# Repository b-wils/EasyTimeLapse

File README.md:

# Easy Time Lapse

Easy Time Lapse (ETL) is device that allows enables you DSLR camera to capture timelapses. 

You can read on overview of the project here-
https://web.archive.org/web/20150224155257/http://nerdtribe.blog.com:80/easy-time-lapse
https://web.archive.org/web/20130428181341/http://scramblor.posterous.com

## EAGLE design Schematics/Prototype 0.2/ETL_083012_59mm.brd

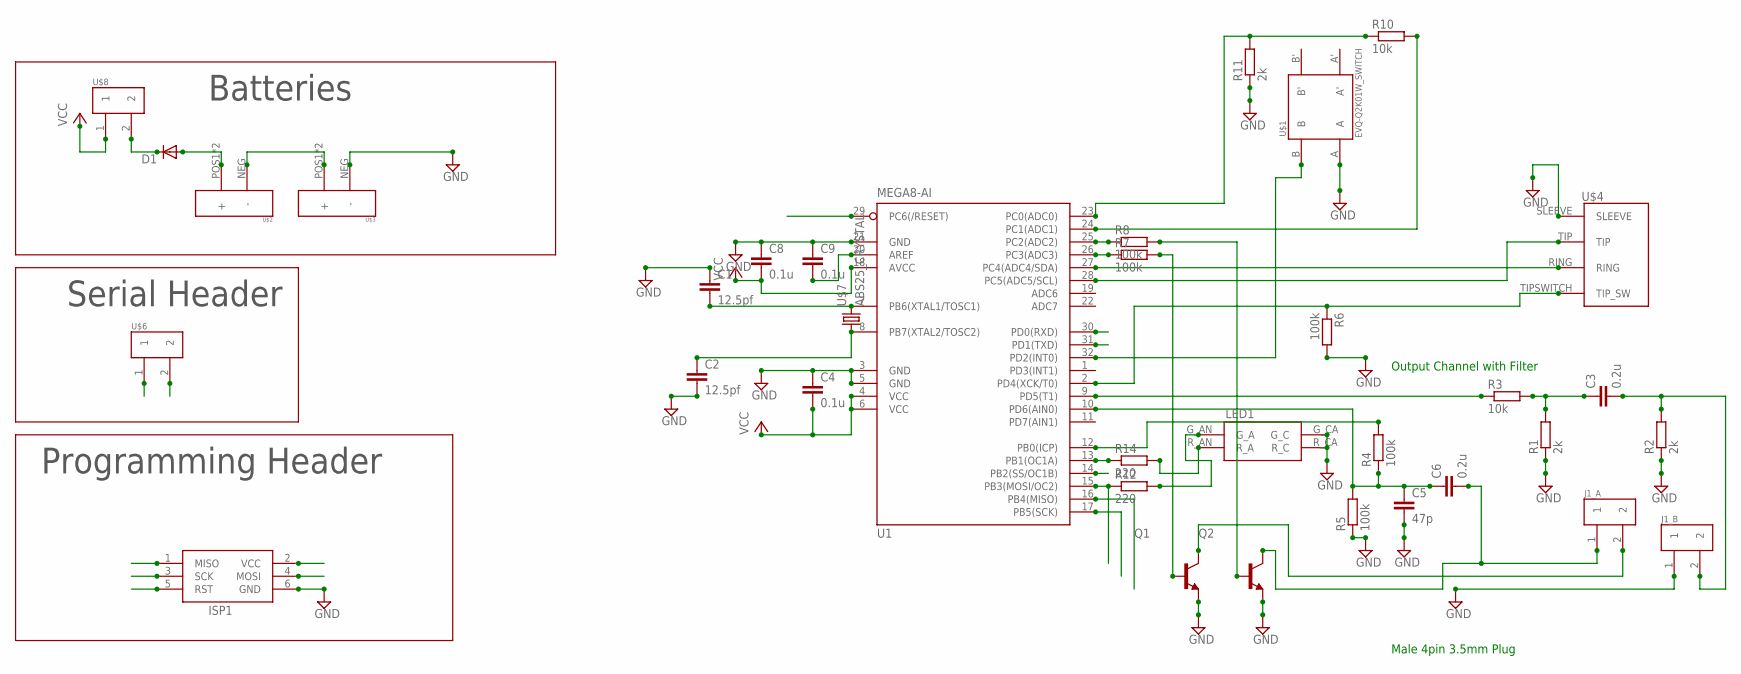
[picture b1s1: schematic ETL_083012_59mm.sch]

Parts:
C1, C2: 12.5pf; C0402
C3, C6: 0.2u; C0402
C4, C8, C9: 0.1u; C0402
C5: 47p; C0402
D1: DIODE-SOD323-R; SOD323-R
ISP1: AVRISP-6; AVRISP
J1_A, J1_B: SERIAL_2_VERT
LED1: LED_BI_RG; LED_BI_1210
Q1, Q2: BC847-NPN-SOT23-BEC; SOT23-BEC
R1, R2, R11: 2k; R0402
R3, R10: 10k; R0402
R4, R5, R6, R7, R8: 100k; R0402
R12, R14: 220; R0402
U1: MEGA8-AI; TQFP32-08
U$1: EVQ-Q2K01W_SWITCH
U$2, U$3: 22M2620_BATTHOLDER
U$4: SJ-3524-SMT_AUDIOJACK
U$6, U$8: SERIAL_2_VERT
U$7: ABS25_CRYSTAL

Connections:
GND: C1.1, C2.2, C4.1, C5.2, C8.1, C9.1, ISP1.6 (GND), J1_B.1, LED1.G_CA (G_C), LED1.R_CA (R_C), Q1.E, Q2.E, R1.1, R2.1, R5.1, R6.2, R11.1, U1.3 (GND), U1.5 (GND), U1.21 (GND), U$1.A, U$3.NEG (-), U$4.SLEEVE
MISO: ISP1.1 (MISO), U1.16 (PB4(MISO))
MOSI: ISP1.4 (MOSI), R12.1, U1.15 (PB3(MOSI/OC2))
unnamed: C1.2, U1.7 (PB6(XTAL1/TOSC1)), U$7.4 (2)
unnamed: C2.1, U1.8 (PB7(XTAL2/TOSC2)), U$7.1
unnamed: R14.1, U1.13 (PB1(OC1A))
unnamed: LED1.G_AN (G_A), R12.2
unnamed: D1.C, U$8.2
unnamed: LED1.R_AN (R_A), R14.2
unnamed: R3.1, U1.9 (PD5(T1))
unnamed: C5.1, C6.1, R4.1, R5.2, U1.10 (PD6(AIN0))
unnamed: C3.1, R1.2, R3.2
unnamed: C3.2, J1_B.2, R2.2
unnamed: R8.1, U1.25 (PC2(ADC2))
unnamed: R10.2, U1.24 (PC1(ADC1))
unnamed: R7.1, U1.26 (PC3(ADC3))
unnamed: U$2.NEG (-), U$3.POS1 (+), U$3.POS2 (+)
unnamed: C9.2, U1.20 (AREF)
unnamed: R10.1, R11.2, U1.23 (PC0(ADC0))
unnamed: Q1.B, R7.2
unnamed: Q2.B, R8.2
unnamed: U1.32 (PD2(INT0)), U$1.B
unnamed: D1.A, U$2.POS1 (+), U$2.POS2 (+)
unnamed: J1_A.2, Q1.C
unnamed: C6.2, J1_A.1, Q2.C
unnamed: R4.2, U1.12 (PB0(ICP))
PC4: U1.27 (PC4(ADC4/SDA)), U$4.RING
PC5: U1.28 (PC5(ADC5/SCL)), U$4.TIP
PD0: U1.30 (PD0(RXD)), U$6.1
PD1: U1.31 (PD1(TXD)), U$6.2
PD4: R6.1, U1.2 (PD4(XCK/T0)), U$4.TIPSWITCH (TIP_SW)
RESET: ISP1.5 (RST), U1.29 (PC6(/RESET))
SCK: ISP1.3 (SCK), U1.17 (PB5(SCK))
VCC: C4.2, C8.2, ISP1.2 (VCC), U1.4 (VCC), U1.6 (VCC), U1.18 (AVCC), U$8.1

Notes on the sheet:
Output Channel with Filter
Male 4pin 3.5mm Plug
Batteries
Serial Header
Programming Header

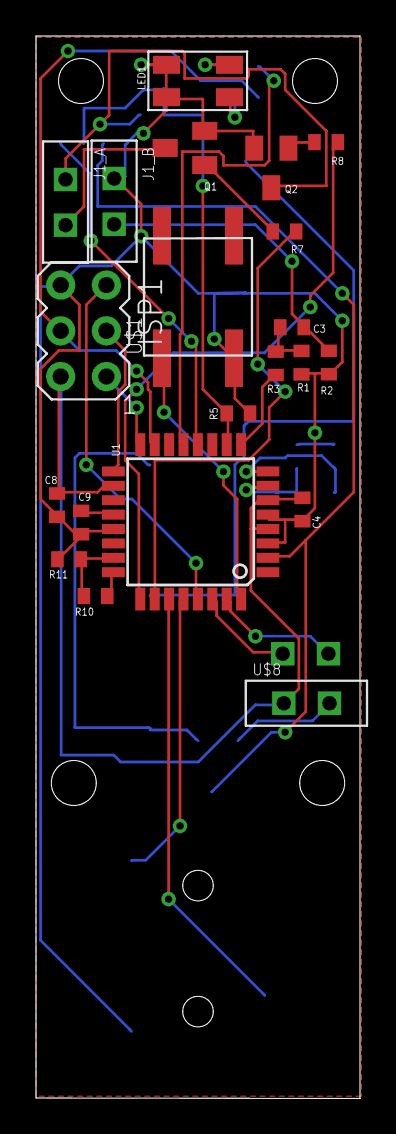
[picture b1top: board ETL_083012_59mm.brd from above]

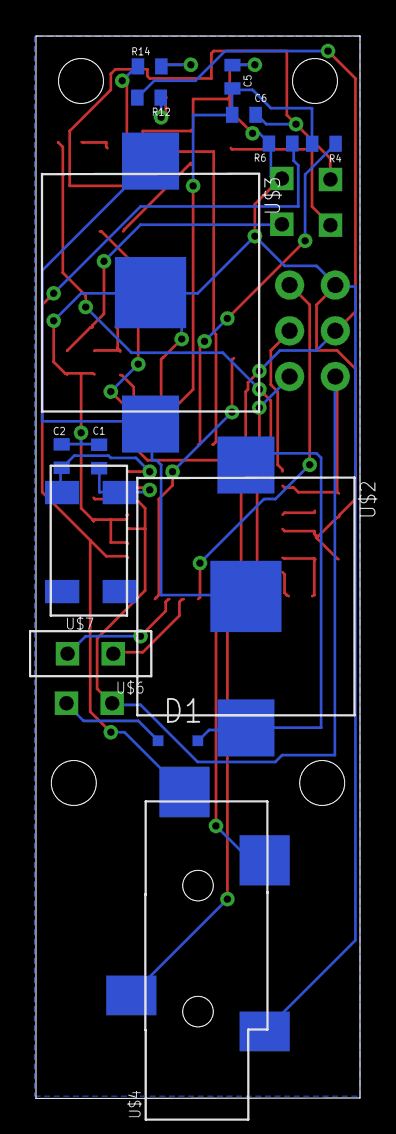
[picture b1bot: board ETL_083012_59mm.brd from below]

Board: 2 copper layers, 18.0 x 59.0 mm, 35 parts (14 on the bottom side), 34 nets.

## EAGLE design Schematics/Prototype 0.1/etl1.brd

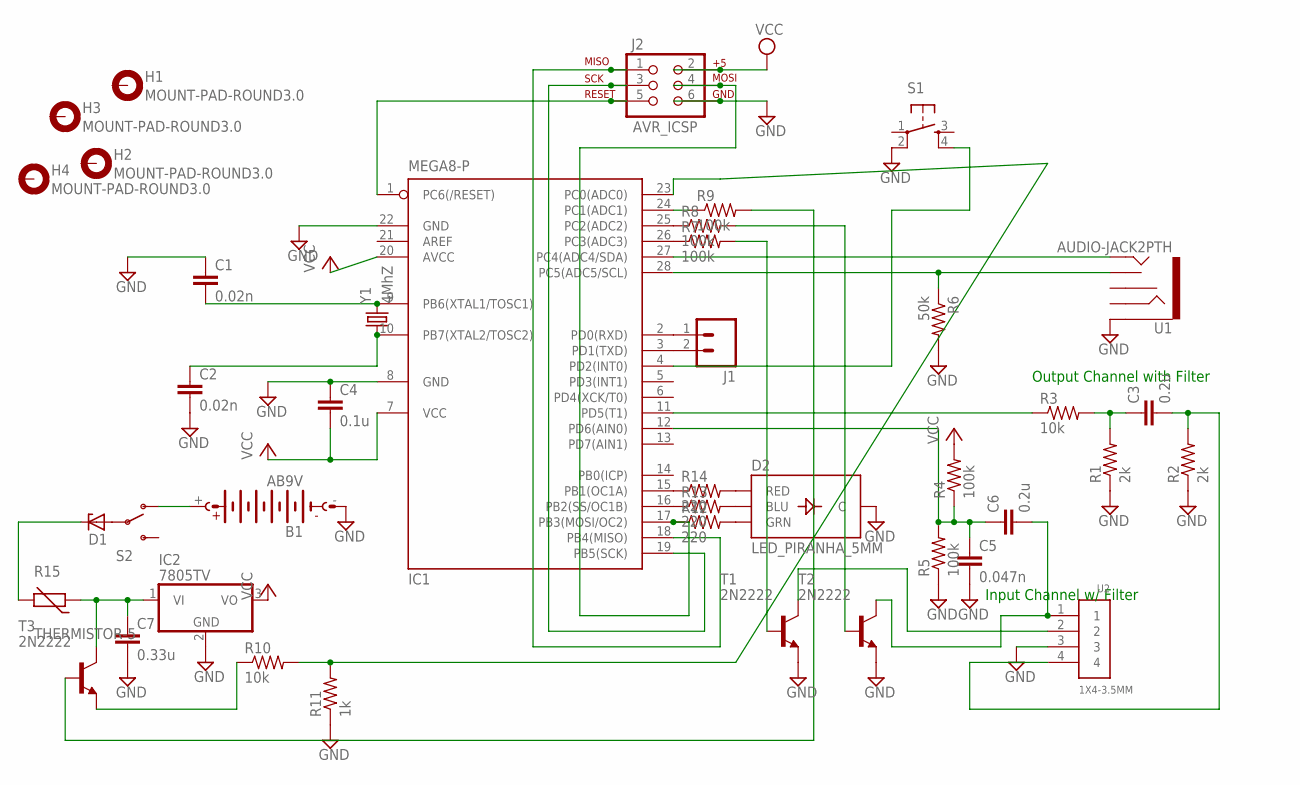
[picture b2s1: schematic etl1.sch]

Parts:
B1: AB9V
C1, C2: 0.02n; C5B3
C3, C6: 0.2u; C5B3
C4: 0.1u; C5B3
C5: 0.047n; C5B3
C7: 0.33u; C5B3
D1: ZENER-DIODEZD-10; ZDIO-10
D2: LED_PIRANHA_5MM
H1, H2, H3, H4: MOUNT-PAD-ROUND3.0; 3,0-PAD
IC1: MEGA8-P; DIL28-3
IC2: 7805TV; TO220V
J1: M02LOCK; 1X02_LOCK
J2: AVR_ICSP; 2X3-NS
R1, R2: 2k; 0207/10
R3, R10: 10k; 0207/10
R4, R5, R7, R8, R9: 100k; 0207/10
R6: 50k; 0207/10
R11: 1k; 0207/10
R12, R13, R14: 220; 0207/10
R15: THERMISTOR-5; R-5
S1: TAC_SWITCHPTH; TACTILE-PTH
S2: SWITCH-SPDTPTH; SWITCH-SPDT
T1, T2, T3: 2N2222; TO92-EBC-OVAL
U1: AUDIO-JACK2PTH; AUDIO-JACK
U2: 1X4-3.5MM; 1X04-3.5MM
Y1: 4MhZ; HC49US

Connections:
GND: B1.-, C1.1, C2.2, C4.1, C5.2, C7.2, D2.- (C), IC1.8 (GND), IC1.22 (GND), IC2.2 (GND), J2.6, R1.1, R2.1, R5.1, R6.2, R11.1, S1.2, T1.E, T2.E, U1.SLEEVE, U2.3
unnamed: C1.2, IC1.9 (PB6(XTAL1/TOSC1)), Y1.2
unnamed: C2.1, IC1.10 (PB7(XTAL2/TOSC2)), Y1.1
unnamed: IC1.16 (PB2(SS/OC1B)), R13.1
unnamed: IC1.15 (PB1(OC1A)), R14.1
unnamed: IC1.17 (PB3(MOSI/OC2)), J2.4, R12.1
unnamed: D2.G (GRN), R12.2
unnamed: D2.B (BLU), R13.2
unnamed: D2.R (RED), R14.2
unnamed: IC1.11 (PD5(T1)), R3.1
unnamed: C5.1, C6.1, IC1.12 (PD6(AIN0)), R4.1, R5.2
unnamed: C3.1, R1.2, R3.2
unnamed: C3.2, R2.2, U2.4
unnamed: D1.A, S2.2
unnamed: D1.C, R15.2
unnamed: C7.1, IC2.1 (VI), R15.1, T3.C
unnamed: IC1.24 (PC1(ADC1)), R9.1
unnamed: IC1.26 (PC3(ADC3)), R7.1
unnamed: IC1.25 (PC2(ADC2)), R8.1
unnamed: IC1.27 (PC4(ADC4/SDA)), U1.TIP
unnamed: IC1.28 (PC5(ADC5/SCL)), R6.1, U1.TSH
unnamed: R10.1, T3.E
unnamed: IC1.23 (PC0(ADC0)), R10.2, R11.2
unnamed: R9.2, T3.B
unnamed: R7.2, T1.B
unnamed: R8.2, T2.B
unnamed: IC1.4 (PD2(INT0)), S1.4
unnamed: B1.+, S2.1 (O)
unnamed: T1.C, U2.2
unnamed: C6.2, T2.C, U2.1
unnamed: IC1.18 (PB4(MISO)), J2.1
unnamed: IC1.19 (PB5(SCK)), J2.3
unnamed: IC1.1 (PC6(/RESET)), J2.5
unnamed: IC1.2 (PD0(RXD)), J1.1
unnamed: IC1.3 (PD1(TXD)), J1.2
VCC: C4.2, IC1.7 (VCC), IC1.20 (AVCC), IC2.3 (VO), J2.2, R4.2

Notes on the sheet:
Input Channel w/ Filter
Output Channel with Filter

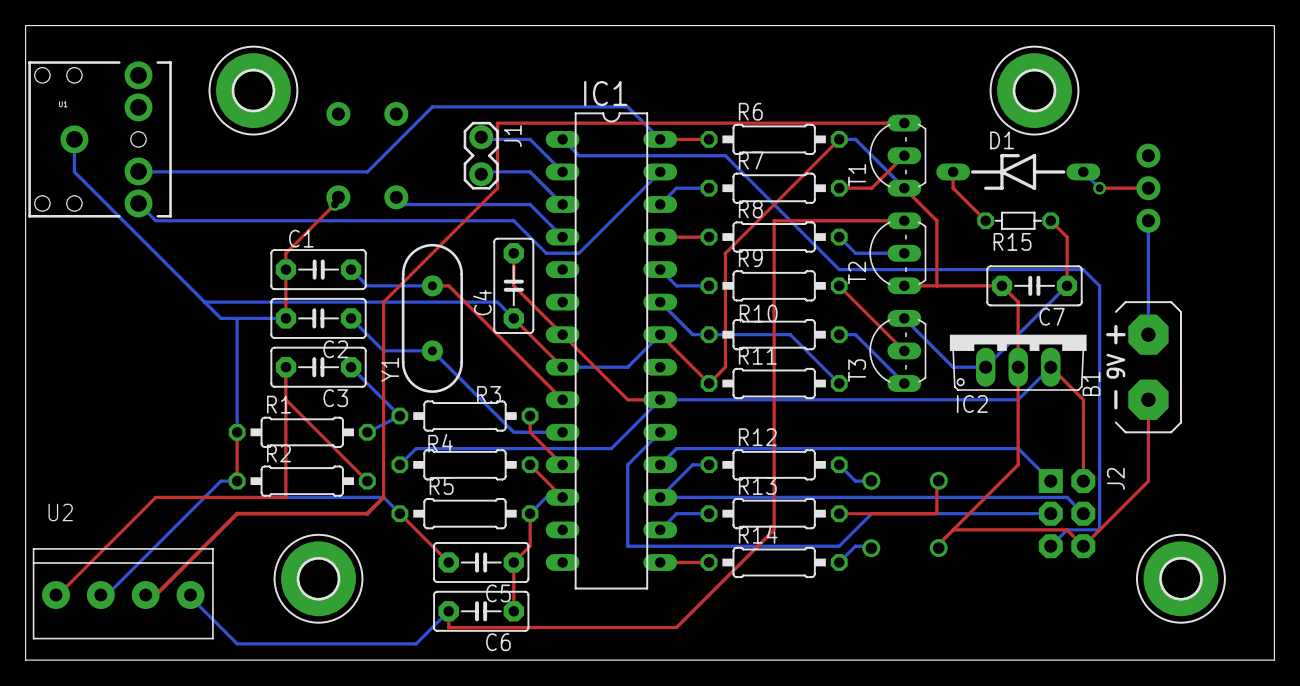
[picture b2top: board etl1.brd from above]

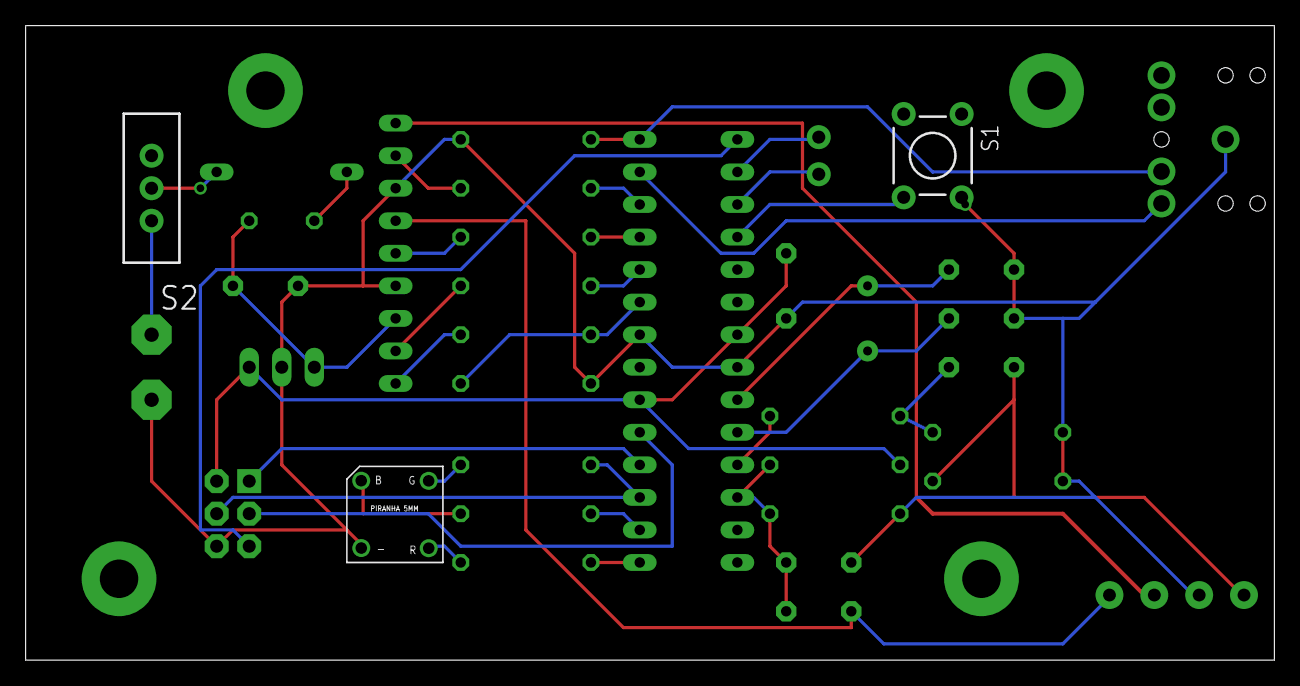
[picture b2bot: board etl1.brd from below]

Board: 2 copper layers, 97.5 x 49.5 mm, 41 parts (3 on the bottom side), 36 nets.

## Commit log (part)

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2011-09-18 Automatically created readme.textile and /trunk directory. We recommend you to put all your code there.
2012-06-25 Moving ETL_Firmware and etl_iphone to trunk
2012-06-25 Adding communications and ETL-interface-test projects
2012-06-25 adding .xibs
2012-06-27 Adding root .gitignore
    Adding Sliders version of the Timelapse view
2012-06-27 Added some reflection magic to load controller/view combos based on class name.
2012-06-28 Updated layout of bulb page per discussion, this is the simple version with all manual input
2012-06-28 Wired Bulb ramp controls
2012-06-29 Adding BulbSettings for bulb ramping
2012-06-29 Moved assets folder to trunk
2012-06-29 Adding initial asset files
2012-06-29 Adding background images to all screens
2012-06-29 Removed navigation toolbars and replaced with simple 'Back' buttons
2012-06-29 Added topbar image view to all main pages
2012-06-29 Adding placeholder assets
2012-06-29 Updated topbar assets with correct text
2012-06-29 Home buttons, initial state (unpressed)
2012-06-29 Home buttons, pressed state
2012-06-29 Home buttons, unpressed (fixed size)
2012-06-30 Added images to home screen buttons
2012-06-30 Adding indented panel graphics (top 2px, middle section, bottom 1px)
2012-06-30 Timelapse shot detail field background
2012-07-03 Adding a slew of assets for progress bar, back button, sliders, switches, settings
2012-07-03 Custom switch (in-progress) and progress bar.
2012-07-03 Two way communication with iphone. includes Crc checking and retry protocol.
2012-07-04 Using Common.h instead of etl_typedefs.h. Updated structure definition style in Common.h to avoid Xcode compiler errors.
2012-07-05 New switches with thumb piece for correct interaction
2012-07-05 Change to communications classes
2012-07-05 Added directory "ETL-comm-test"
2012-07-05 Removing "ETL-comm-test"
2012-07-05 Importing ETL-comm-test
2012-07-05 Adjusted layout, resized buttons
2012-07-05 Adding back button that reads "home"
2012-07-05 Fixing some sync issues
2012-07-05 Adding struct packing for iphone
2012-07-06 First pass at longer packets
2012-07-06 Custom slider graphics
2012-07-06 [IOS] Long packets for device
2012-07-06 [ETL] Long packets for device
2012-07-09 [ETL] First run at processing different packet types. Untested.
2012-07-09 Split Utils function definitions into it's own file
2012-07-09 Added two splash screen placeholders (Default.png / Default@2x.png)
2012-07-09 Added post programming screen
2012-07-09 Initial storyboard implementation
2012-07-09 Removing .xib files that have been ported to storyboard
2012-07-11 Asset dump. This should completes all assets v1, now will work on color pass. Also included PSD folder.
2012-07-11 (and deleted old ones)
2012-07-11 [ETL] Memory optimizations
2012-07-11 [ETL] Moving to Atmel Studio 6
2012-07-11 [ETL] Splitting camera and communications code to their own files.
2012-07-12 [ETL] Assemble configs from multiple packets
2012-07-12 [IOS] Send configs in multiple packets
2012-07-12 [ETL] Cleaning up unused/unneeded code.
2012-07-12 Initial audio unit input
2012-07-12 iPhone and iPad receive working
2012-07-12 Working on iPhone 4
2012-07-12 Color pass on most assets. Still working on home screen core buttons.
2012-07-12 Adding unit tests for ETL
2012-07-14 Adding external testing dependencies
2012-07-14 Initial tests. Integrated some new art assets
2012-07-14 Unit testing for Timelapse, TimelapseController, and Model
2012-07-16 renaming back to home button to eliminate confusion
2012-07-16 updated home screen with new buttons & text
2012-07-16 [ETL] Bug: During low power, Timer2 overflows twice before ISR runs. Result- time is tracked at half speed
2012-07-17 Initial communication cycle between phone and device in main app working
2012-07-17 Fixing home screen button images
2012-07-17 Programming finishes sucessfully
2012-07-17 [ETL] Reduce power consumption
2012-07-17 [ETL] FSK VCC filter Res connected to pin instead of power rail.
2012-07-18 Builds without warnings, added Hamcrest matchers for testing
2012-07-18 Added new definitions for ETL to send info to IOS
2012-07-18 Case fixing
2012-07-18 [ETL] Additional communication commands
2012-07-18 [IOS] Additional communications commands
2012-07-18 testing out some dark (high contrast) back buttons
2012-07-19 corrected asset size
2012-07-19 new assets, pads incl how to screen
2012-07-19 adding "settings" top bar asset
2012-07-19 [ETL] Device goes to idle if no communication is received after 15 seconds
2012-07-19 updated storyboards with new interaction, settings screen, text fields, settings buttons, and refined ux.
2012-07-19 [ETL] Added manual release mode, with escape to transmit
2012-07-24 [ETL] Device can be set into manual mode from phone
2012-07-24 [ETL] Prototype code for external async timer. Not turned on yet.
2012-07-24 [ETL] Update serial prints (for debugging) to be configurable
2012-07-24 Animated switching between keyboard and picker on TL screen
2012-07-24 Fixed the non-stoppable audio issues
2012-07-24 Programming from the manual screen will enable manual mode
2012-07-25 Timelapse and Hdr UI improvments. 'Unlimited' length timelapse
2012-07-25 Asset revisions for back buttons (higher contrast) & text fields
2012-07-25 Initial HDR programming implementation
2012-07-25 Improved integration between HDR and Timelapse controllers
2012-07-25 [ETL] Fixed HDR settings
2012-07-26 [ETL] Fixed bug with flash feedback/HDR exposure time.
2012-07-26 Updates to "remote" flow, manual, and bimodal. Also added pre-programming instructions (hold button down)
2012-07-26 New assets to go with last checkin
2012-07-26 Project file updates w/ assets for storyboard
2012-07-30 [ETL] Fixing battery level bug, updating state changes
2012-07-30 Settings buttons and back buttons all wired
2012-07-31 Back vs. Home logic
2012-07-31 [ETL] Fixing bulb ramp bugs, interactions; prints don't take up memory!
2012-07-31 Enabled pre-programming screen and fixed timing bug for completion packet sending.
2012-07-31 Fixed bug in HDR wiring
2012-07-31 Custom switch images.
2012-07-31 [ETL] Store and load settings from EEPROM
2012-07-31 [ETL] Decide to use bramp cable on the fly
2012-07-31 [ETL] Fixed bug where additional first shot data was cleared during transmit
2012-08-01 [ETL] Pause after exposure change click, reduce LED brightness
2012-08-01 Storyboard changes: manual layout, bulb layout (not final), bimodal layout, back button changes, spacing changes on nearly every page
2012-08-01 Done, Ready, Cancel buttons adjusted and changed on storyboard
2012-08-01 [ETL] Adding error/idle retry to communication protocol
2012-08-01 [IOS] Transmission error testing
2012-08-01 Fixed initial value display for HDR
    Re-created ETLStopList and ETLPickerView. Caused picker to select closest fStop when in ms mode.
2012-08-01 [ETL] Adding support for press to advance/pause timelapse
2012-08-01 Instructions screens added, PSD also
2012-08-02 [ETL] Support interval deramp during press on ramp
2012-08-02 Updated storyboard with Done/Next buttons. Done Programming Controller still needs conditional logic for turning tips off (setting), if we choose to implement that feature.
2012-08-02 [ETL] Move bit manipulation to common.h
2012-08-02 Possibly final storyboard layout and art-wise. New PSDs for assets as well.
2012-08-06 [ETL] Communications improvements
2012-08-06 Re-added ETLTimeUnitList and added ETLPickerList base class
    Initial support and testing for componentized interval selection controls
    Testing framework tweaks
    IntervalSelectionController works.
2012-08-06 Bimodal programming support
2012-08-07 Initial stop selection component implementation (picker shows)
    Stop selection controller working with HDR
    HDR data synchronization. UI switch replacement generalization
2012-08-07 Initial blub control wiring
2012-08-07 [ETL] Bulb ramp shutter lag can be set from phone
2012-08-07 Bulb view auto-scrolling
2012-08-07 Initial bulb ramp programming functionality
2012-08-07 Fixing timing error in Bulb programming
2012-08-07 [ETL] Update micros() to reflect new timing, reduce transmit delay
2012-08-07 Fixing bug w/ packet repair which caused resending of incorrect packet #
2012-08-08 Resolving pre-programming cancel audio bug
2012-08-08 Settings persistence support and flash delay transmission
2012-08-08 [ETL] Fixed bug where manual mode would not release shutter during transmit
2012-08-08 updated storyboard to hide settings elements except for flash offset, and to allow for programatic type (label) on the pre-programming screen; updated accompanying preprogramming pngs.
2012-08-08 [ETL] Actually populate device info packet
2012-08-08 [IOS] Add _BV definitions to common for iPhone
2012-08-08 [ETL] Bug fix - actually return the battery level...
2012-08-09 Simple microphone detection
2012-08-09 [ETL] Auto start after programming, first pass
2012-08-09 [IOS] Bug fix - Timelapse exposure not set
2012-08-09 Fix crashing bug when repeatedly plugging/unplugging audio jack
2012-08-09 [ETL] led strength, bulb lag, buffer recover time setable from phone, stored/retrieved in eeprom across power cycle
2012-08-09 [ETL] Fixed bug with storing configs, idle is configurable
2012-08-13 rollback typo
2012-08-13 Sync with latest firmware
2012-08-14 Resolves issue #4. Bracket count wired appropriately in HDR controller
2012-08-14 [ETL] Fixed bug where HDR timelapse would not use correct interval
2012-08-14 couple of new assets for battery indication
2012-08-14 bulb sunrise/sunset screen, buffer recover time in settings
2012-08-14 battery indicator added on programming screen
2012-08-15 [ETL] Pressing to change uses the new interval for next shot time
2012-08-15 Fixes #7: Should set a default value for flash offset (35ms)
    Fixes #18: Should use a better app name
    Fixes #8: Add buffer recover time in settings
2012-08-15 Follow on for issue #8 to fix settings screen ui
2012-08-15 updated storyboard and related assets to unify the way we refer to device as "device" (not ETL, ETL device, or time-lapse device); also updated ready button sizes
2012-08-15 Fixes? #11: Sunrise - no way to do
2012-08-15 Fixes #17: Insconsistent references to device/ETL/ETL device
2012-08-15 Updated bulb sunrise/sunset pressed states
2012-08-15 Resolves #20: Send default values for LED strength, idle settings
2012-08-15 Resolves #20: Buffer recover time not persisted after change
2012-08-15 Resolves #14: HDR timelapse default interval should account for buffer. Also fixes other aspects of default interval and misc. other issues.
2012-08-15 Resolved #22: Sunrise - set default exposure to higher value (4s)
2012-08-15 Resolves #6v2. Doesn't send 0 shot timelapse packets
2012-08-16 Battery level indication
2012-08-16 Fix for initial packet CRC errors not supplying battery info. Only works once (2 crc errors still fails).
2012-08-17 [ETL] Communications, LED improvements
2012-08-20 Resolves #23: App crash in timelapse
2012-08-20 Resolves #24: iPhone sound plays during programming if no device plugged in
2012-08-22 Initial Timelapse screen UI revamp
2012-08-23 Inital rename from ETL-interface-test to ETL
    Moved source files from ETL-interface-test/ to ETL/
2012-08-23 Beta Timelapse interaction, easy mode, first pass.
2012-08-23 Fixing typo
2012-08-27 Initial implementation of ramp view
2012-09-10 Kickstarter mock assets for the time lapse screen (radial dial, no keyboard yet)
2012-09-10 Adding bulb assets
2012-09-20 Sexier bulb ramp view
2012-09-20 Value popups
2012-09-20 Timelapse programming works with new screen
2012-09-20 Radial slider + initial unit menu impl
2012-09-20 Rotated radial slider
2012-09-20 Sexy slidey value editor
2012-09-22 Hacky radial slider animation
2012-09-22 programming screens update
2012-09-24 [ETL] Changes for new mini-pcb
2012-09-25 Updated pressed state
2012-09-25 [ETL] Changes to user the external 32768 clock on async timer 2.
2012-09-26 unit picker styling
2012-09-28 updated assets for status screen
2012-09-30 UI cleanup
2012-10-08 Bulb ramp visual styling
2012-10-16 Updating .gitignore
2012-10-16 git ignore updates

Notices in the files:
parts and their libraries:
SparkFun-Connectors: Licensing: CC v3.0 Share-Alike You are welcome to use this library for commercial purposes.
